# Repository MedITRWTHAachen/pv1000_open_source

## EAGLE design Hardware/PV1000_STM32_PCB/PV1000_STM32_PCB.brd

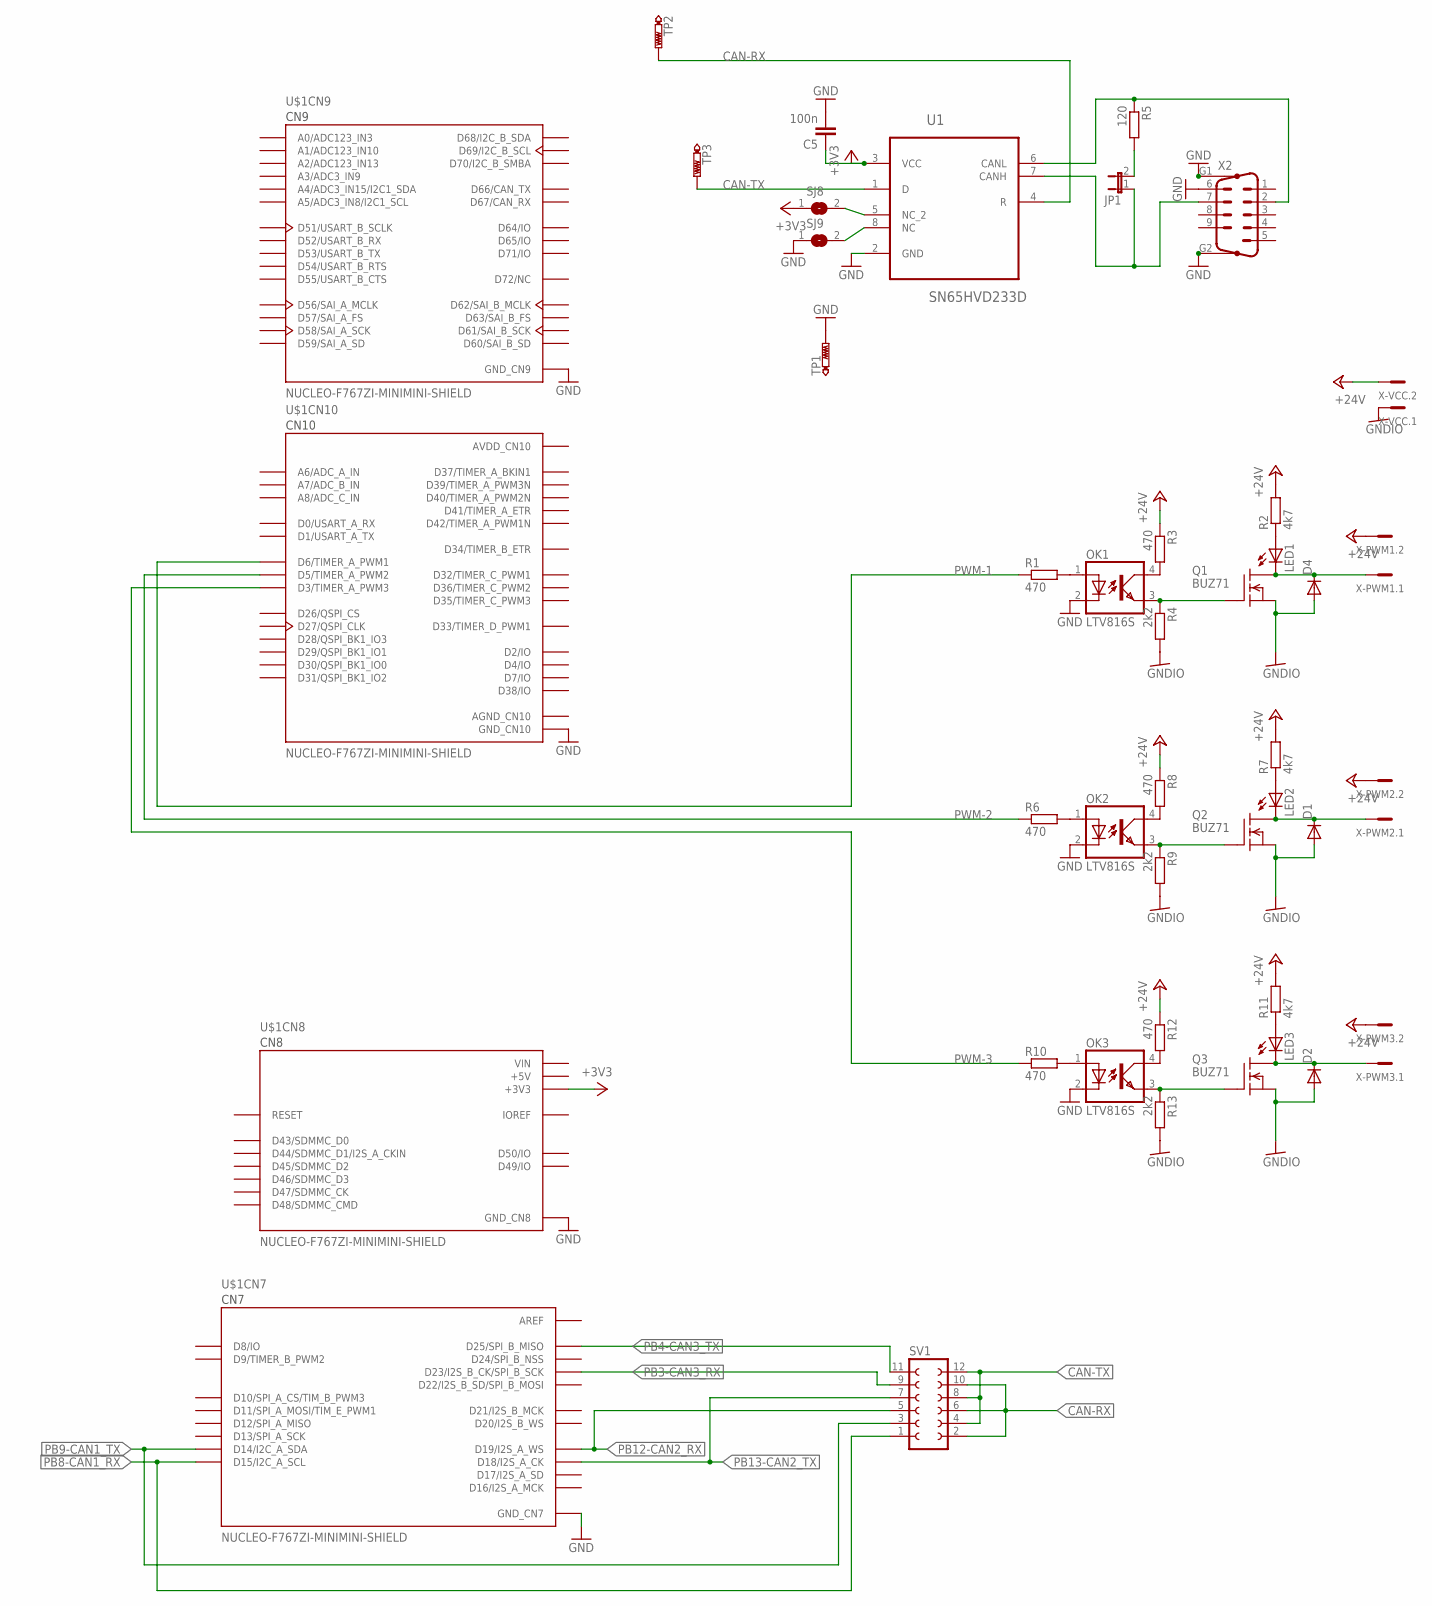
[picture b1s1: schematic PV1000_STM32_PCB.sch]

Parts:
C5: 100n; C0805
D1, D2, D4: DIODE-D-5; D-5
JP1: JP1E; JP1
LED1, LED2, LED3: LEDCHIP-LED0805; CHIP-LED0805
OK1, OK2, OK3: LTV816S; SMD4
Q1, Q2, Q3: BUZ71; TO220
R1, R3, R6, R8, R10, R12: 470; M0805
R2, R7, R11: 4k7; M0805
R4, R9, R13: 2k2; M0805
R5: 120; R0603
SJ8, SJ9: SJ0603
SV1: FE06-2
TP1, TP2, TP3: PTR1PAD1-13Y; P1-13Y
U1: SN65HVD233D; SOIC127P600X175-8N
U$1: NUCLEO-F767ZI-MINIMINI-SHIELD; ST_NUCLEO-F767ZI-MIN
X2: M09HPFARNELL; M09HP-9_2
X-PWM1, X-PWM2, X-PWM3: MC2
X-VCC: MC2

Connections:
+3V3: C5.1, SJ8.1, U1.3 (VCC), U$1.CN8_7 (+3V3)
+5V: U$1.CN8_9 (+5V)
+24V: R2.2, R3.1, R7.2, R8.1, R11.2, R12.1, X-PWM1.2, X-PWM2.2, X-PWM3.2, X-VCC.2
AGND_CN10: U$1.CN10_3 (AGND_CN10)
AREF: U$1.CN7_6 (AREF)
AVDD_CN10: U$1.CN10_1 (AVDD_CN10)
CAN-RX: SV1.2, SV1.6, SV1.10, TP2.TP, U1.4 (R)
CAN-TX: SV1.4, SV1.8, SV1.12, TP3.TP, U1.1 (D)
GND: C5.2, OK1.2 (C), OK2.2 (C), OK3.2 (C), SJ9.1, TP1.TP, U1.2 (GND), U$1.CN7_8 (GND_CN7), U$1.CN8_11 (GND_CN8), U$1.CN8_13 (GND_CN8), U$1.CN9_12 (GND_CN9), U$1.CN9_23 (GND_CN9), U$1.CN10_5 (GND_CN10), U$1.CN10_17 (GND_CN10), U$1.CN10_22 (GND_CN10), U$1.CN10_27 (GND_CN10), X2.6, X2.G1, X2.G2
GNDIO: D1.A, D2.A, D4.A, Q1.3 (S), Q2.3 (S), Q3.3 (S), R4.2, R9.2, R13.2, X-VCC.1
unnamed: JP1.1, U1.7 (CANH), X2.7
unnamed: OK1.1 (A), R1.2
unnamed: SJ8.2, U1.5 (NC_2)
unnamed: LED1.A, R2.1
unnamed: OK1.4 (COL), R3.2
unnamed: OK1.3 (EMIT), Q1.1 (G), R4.1
unnamed: SJ9.2, U1.8 (NC)
unnamed: D4.C, LED1.C, Q1.2 (D), X-PWM1.1
unnamed: OK2.1 (A), R6.2
unnamed: OK2.4 (COL), R8.2
unnamed: OK2.3 (EMIT), Q2.1 (G), R9.1
unnamed: D1.C, LED2.C, Q2.2 (D), X-PWM2.1
unnamed: LED2.A, R7.1
unnamed: OK3.1 (A), R10.2
unnamed: OK3.4 (COL), R12.2
unnamed: OK3.3 (EMIT), Q3.1 (G), R13.1
unnamed: D2.C, LED3.C, Q3.2 (D), X-PWM3.1
unnamed: JP1.2, R5.2
unnamed: LED3.A, R11.1
unnamed: R5.1, U1.6 (CANL), X2.2
PB3-CAN3_RX: SV1.9, U$1.CN7_15 (D23/I2S_B_CK/SPI_B_SCK)
PB4-CAN3_TX: SV1.11, U$1.CN7_19 (D25/SPI_B_MISO)
PB8-CAN1_RX: SV1.1, U$1.CN7_2 (D15/I2C_A_SCL)
PB9-CAN1_TX: SV1.3, U$1.CN7_4 (D14/I2C_A_SDA)
PB12-CAN2_RX: SV1.5, U$1.CN7_7 (D19/I2S_A_WS)
PB13-CAN2_TX: SV1.7, U$1.CN7_5 (D18/I2S_A_CK)
PWM-1: R1.1, U$1.CN10_4 (D6/TIMER_A_PWM1)
PWM-2: R6.1, U$1.CN10_6 (D5/TIMER_A_PWM2)
PWM-3: R10.1, U$1.CN10_10 (D3/TIMER_A_PWM3)
VIN: U$1.CN8_15 (VIN)

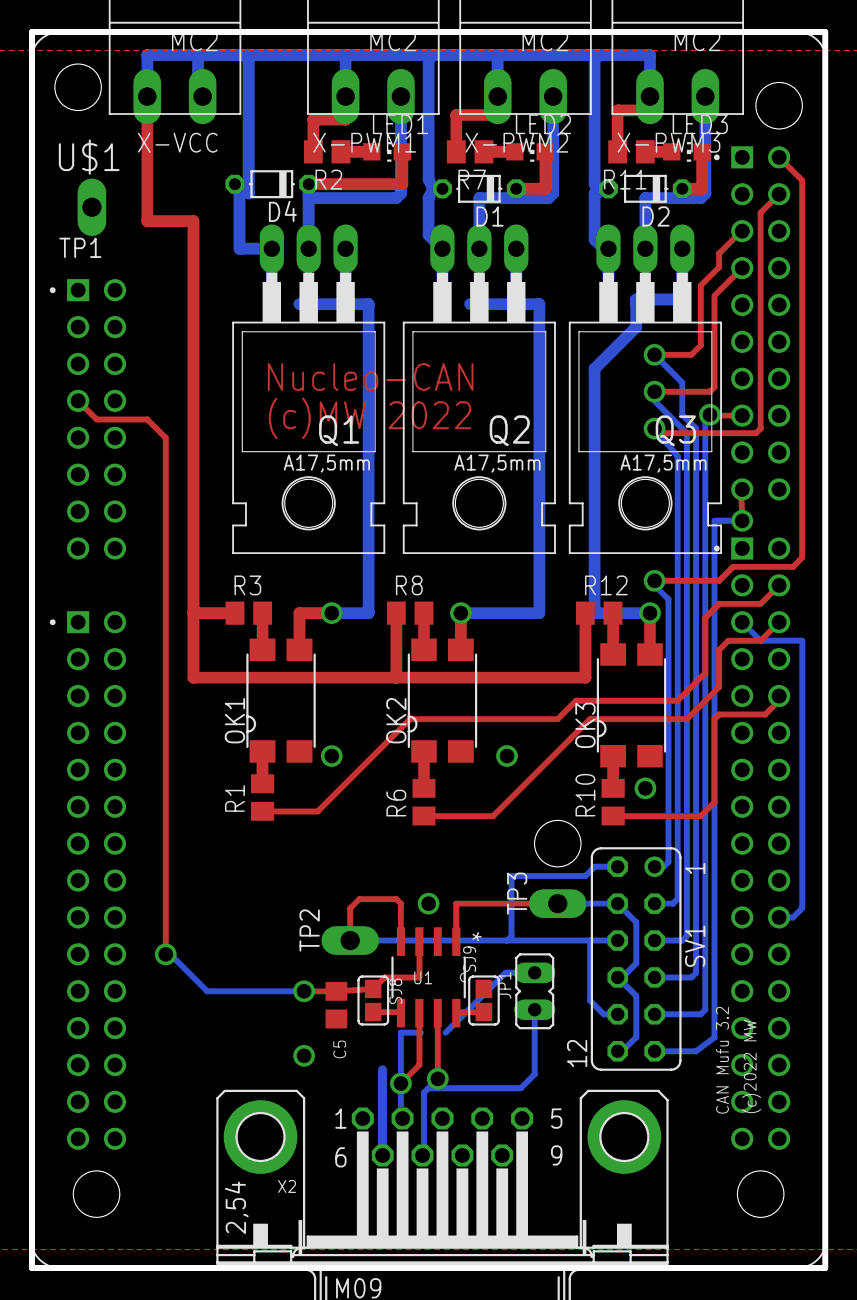
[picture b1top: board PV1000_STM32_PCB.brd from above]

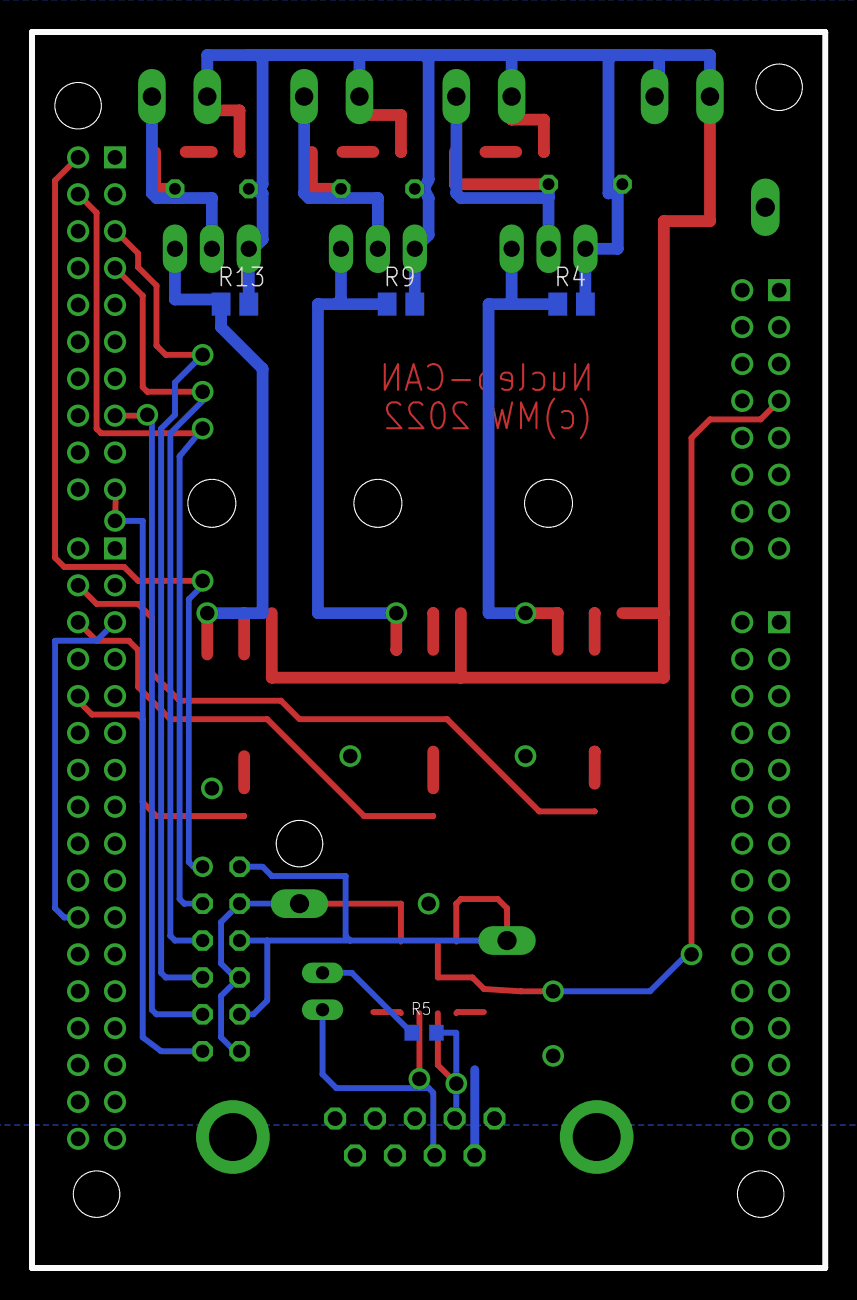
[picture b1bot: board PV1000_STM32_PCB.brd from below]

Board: 2 copper layers, 54.6 x 85.1 mm, 45 parts (4 on the bottom side), 35 nets.

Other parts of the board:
U$2, U$3, U$4, U$5, U$6: PASSMARK

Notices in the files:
Hardware/PV1000_STM32_PCB/PV1000_STM32_PCB.brd:
(c)2022 MW
